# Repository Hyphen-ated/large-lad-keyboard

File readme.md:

## Large Lad Keyboard

148 key hotswap keyboard with a Standard US layout at the core. 

Two rows of function keys, 21 keys to the left, and some extras filling in the top right, along with a rotary encoder.

Nobody is selling this keyboard. KiCad project files are in this repo. If you want one you need to place an order at a PCB fabrication house for the PCB (and the plate. Or get the plate made elsewhere.) I got the plate made as a "PCB" with 1.6mm aluminum; if you want to try FR4 maybe that would work too.

I didn't design a case for this board. I simply attached two pieces of 1/2" square dowel across the top and bottom rows of holes in the plate. If you'd like to design a case I'd be happy to link it here.

* PCB: 146 x 490 mm
* Plate: 167 x 495 mm

Other materials you will need:

* 148x Through-hole diodes (1N4148)
* 147x MX switches and keycaps
* 147x Kailh hotswap sockets
* 1x set of stabilizers for a full sized keyboard
* 1x Rotary encoder, clickable. (The kind used on keyboards.)
* 1x WeAct STM32F411CEU6 V3.1 "Blackpill" (or a similar board with [the same pinout](/blackpill.png)

If I were to make a rev 2 of this, I would enlarge the stab holes in the plate. I had a rough time getting it to fit and I needed to file down a few edges in the plate. I also intended the plate to have (black) soldermask on top, but I messed that up so the top is bare aluminum right now. (The plate also has a few plated holes in it that don't do anything. This was recommended to me as a way to make PCB fab houses less likely to reject the design for not looking like a PCB. I'm not sure why a business would want to not take someone's money in this way, but whatever.)

Assembly: solder in the diodes and encoder on top, sockets and MCU on bottom. (I used peel-away strips for the MCU to help reduce the vertical size of the overall build while having the MCU socketed for easy removal.) Then attach your stabs to the PCB, put the plate on, and put the switches in. The switches are the only thing holding the PCB up. Then figure out how to mount the plate to some kind of case or just use pieces of wood like I did.

It works with QMK firmware, see my fork here: https://github.com/Hyphen-ated/qmk_firmware

The matrix is a bit of an [unholy nightmare](/keyboard-layout-colors.png) at 12x13. It needs to be much squarer than the layout actually is, because there aren't enough pins otherwise.

Loading firmware: 
* On the blackpill, hold BOOT and press NRST, then release both
* Open STM32CubeProgrammer. Make sure it's connected to the blackpill on the right under "usb configuration"
* Click "open file" and load the QMK hex file built for this board
* Click "download"

Shoutouts to [ai03](https://wiki.ai03.com/books/pcb-design/page/pcb-guide-part-1---preparations), https://github.com/piit79/Kicad-STM32, https://github.com/chgray/daprice-keyswitches, https://github.com/daprice/keyswitches.pretty, http://builder.swillkb.com/, http://www.keyboard-layout-editor.com/

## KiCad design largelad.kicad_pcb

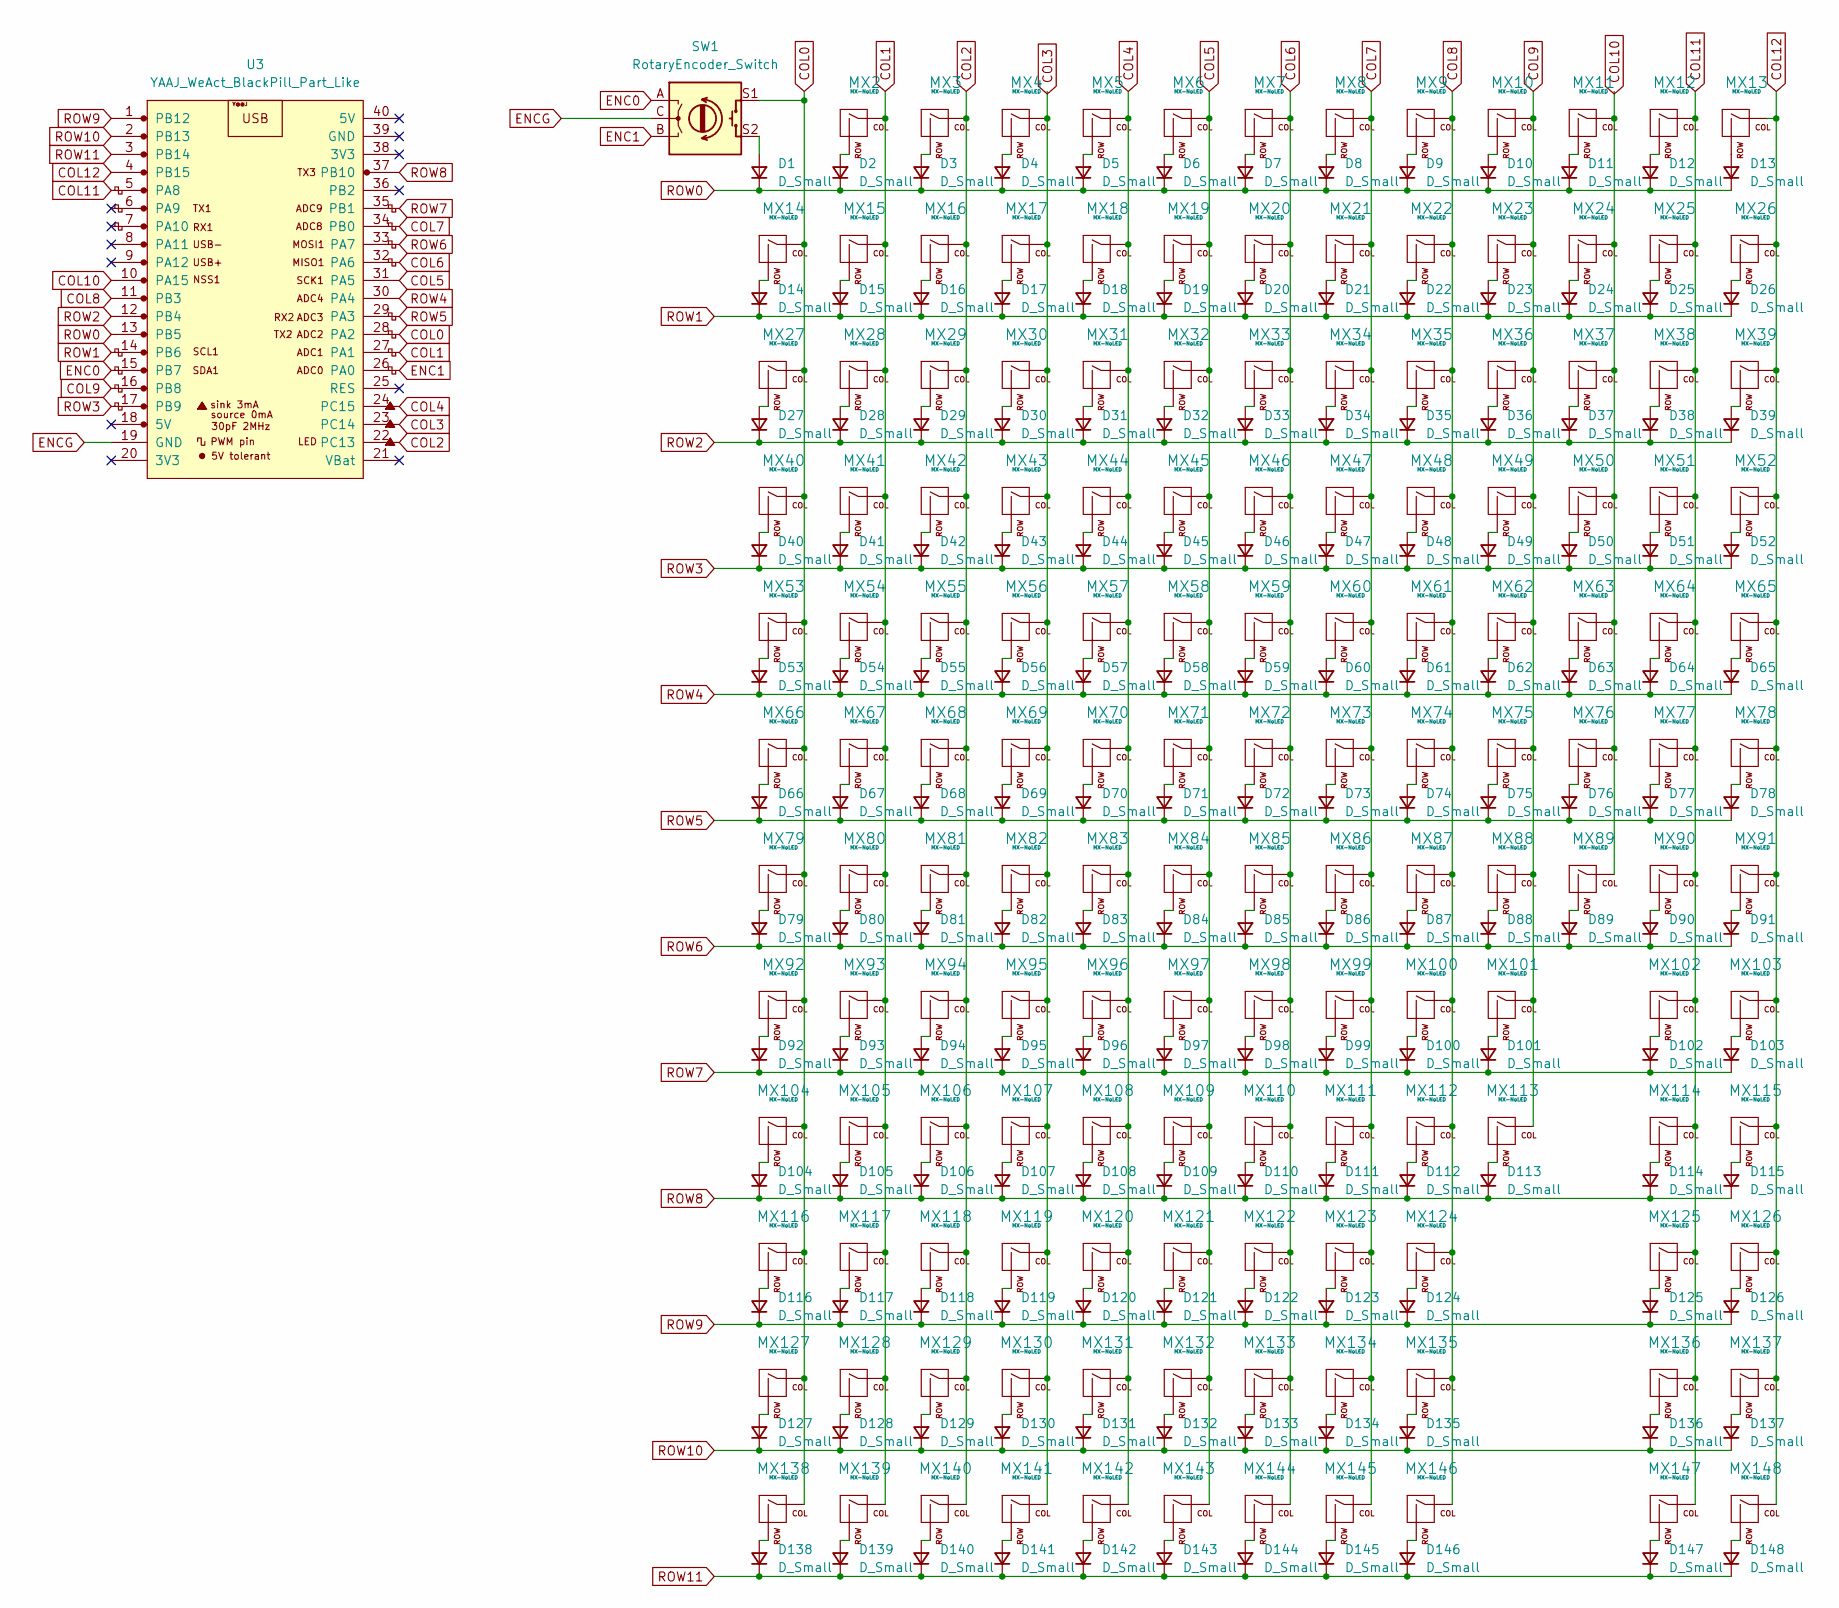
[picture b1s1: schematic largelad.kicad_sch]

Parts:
D1, D2, D3, D4, D5, D6, D7, D8, D9, D10, D11, D12, D13, D14, D15, D16, D17, D18, D19, D20, D21, D22, D23, D24, D25, D26, D27, D28, D29, D30, D31, D32, D33, D34, D35, D36, D37, D38, D39, D40, D41, D42, D43, D44, D45, D46, D47, D48, D49, D50, D51, D52, D53, D54, D55, D56, D57, D58, D59, D60, D61, D62, D63, D64, D65, D66, D67, D68, D69, D70, D71, D72, D73, D74, D75, D76, D77, D78, D79, D80, D81, D82, D83, D84, D85, D86, D87, D88, D89, D90, D91, D92, D93, D94, D95, D96, D97, D98, D99, D100, D101, D102, D103, D104, D105, D106, D107, D108, D109, D110, D111, D112, D113, D114, D115, D116, D117, D118, D119, D120, D121, D122, D123, D124, D125, D126, D127, D128, D129, D130, D131, D132, D133, D134, D135, D136, D137, D138, D139, D140, D141, D142, D143, D144, D145, D146, D147, D148: D_Small; D_DO-35_SOD27_P7.62mm_Horizontal
MX2, MX3, MX4, MX5, MX6, MX7, MX8, MX9, MX10, MX11, MX12, MX13, MX14, MX15, MX16, MX17, MX18, MX19, MX20, MX21, MX22, MX23, MX24, MX25, MX26, MX27, MX28, MX29, MX30, MX31, MX32, MX33, MX34, MX35, MX36, MX37, MX38, MX39, MX40, MX41, MX42, MX43, MX44, MX45, MX46, MX47, MX48, MX49, MX50, MX51, MX52, MX53, MX54, MX55, MX56, MX57, MX58, MX59, MX60, MX61, MX62, MX63, MX64, MX65, MX66, MX67, MX68, MX69, MX70, MX71, MX72, MX73, MX74, MX75, MX76, MX77, MX78, MX79, MX80, MX81, MX82, MX83, MX84, MX85, MX86, MX87, MX88, MX89, MX90, MX91, MX92, MX93, MX94, MX95, MX96, MX97, MX98, MX99, MX100, MX101, MX102, MX103, MX104, MX105, MX106, MX107, MX108, MX109, MX110, MX111, MX112, MX113, MX114, MX115, MX116, MX117, MX118, MX119, MX120, MX121, MX122, MX123, MX124, MX125, MX126, MX127, MX128, MX129, MX130, MX131, MX132, MX133, MX134, MX135, MX136, MX137, MX138, MX139, MX140, MX141, MX142, MX143, MX144, MX145, MX146, MX147, MX148: MX-NoLED; Kailh_socket_MX
SW1: RotaryEncoder_Switch; RotaryEncoder_Alps_EC11E-Switch_Vertical_H20mm_CircularMoun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
U3: YAAJ_WeAct_BlackPill_Part_Like; YAAJ_WeAct_BlackPill_2

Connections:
COL0: MX14.1 (COL), MX27.1 (COL), MX40.1 (COL), MX53.1 (COL), MX66.1 (COL), MX79.1 (COL), MX92.1 (COL), MX104.1 (COL), MX116.1 (COL), MX127.1 (COL), MX138.1 (COL), SW1.S1, U3.28 (PA2)
COL1: MX2.1 (COL), MX15.1 (COL), MX28.1 (COL), MX41.1 (COL), MX54.1 (COL), MX67.1 (COL), MX80.1 (COL), MX93.1 (COL), MX105.1 (COL), MX117.1 (COL), MX128.1 (COL), MX139.1 (COL), U3.27 (PA1)
COL2: MX3.1 (COL), MX16.1 (COL), MX29.1 (COL), MX42.1 (COL), MX55.1 (COL), MX68.1 (COL), MX81.1 (COL), MX94.1 (COL), MX106.1 (COL), MX118.1 (COL), MX129.1 (COL), MX140.1 (COL), U3.22 (PC13)
COL3: MX4.1 (COL), MX17.1 (COL), MX30.1 (COL), MX43.1 (COL), MX56.1 (COL), MX69.1 (COL), MX82.1 (COL), MX95.1 (COL), MX107.1 (COL), MX119.1 (COL), MX130.1 (COL), MX141.1 (COL), U3.23 (PC14)
COL4: MX5.1 (COL), MX18.1 (COL), MX31.1 (COL), MX44.1 (COL), MX57.1 (COL), MX70.1 (COL), MX83.1 (COL), MX96.1 (COL), MX108.1 (COL), MX120.1 (COL), MX131.1 (COL), MX142.1 (COL), U3.24 (PC15)
COL5: MX6.1 (COL), MX19.1 (COL), MX32.1 (COL), MX45.1 (COL), MX58.1 (COL), MX71.1 (COL), MX84.1 (COL), MX97.1 (COL), MX109.1 (COL), MX121.1 (COL), MX132.1 (COL), MX143.1 (COL), U3.31 (PA5)
COL6: MX7.1 (COL), MX20.1 (COL), MX33.1 (COL), MX46.1 (COL), MX59.1 (COL), MX72.1 (COL), MX85.1 (COL), MX98.1 (COL), MX110.1 (COL), MX122.1 (COL), MX133.1 (COL), MX144.1 (COL), U3.32 (PA6)
COL7: MX8.1 (COL), MX21.1 (COL), MX34.1 (COL), MX47.1 (COL), MX60.1 (COL), MX73.1 (COL), MX86.1 (COL), MX99.1 (COL), MX111.1 (COL), MX123.1 (COL), MX134.1 (COL), MX145.1 (COL), U3.34 (PB0)
COL8: MX9.1 (COL), MX22.1 (COL), MX35.1 (COL), MX48.1 (COL), MX61.1 (COL), MX74.1 (COL), MX87.1 (COL), MX100.1 (COL), MX112.1 (COL), MX124.1 (COL), MX135.1 (COL), MX146.1 (COL), U3.11 (PB3)
COL9: MX10.1 (COL), MX23.1 (COL), MX36.1 (COL), MX49.1 (COL), MX62.1 (COL), MX75.1 (COL), MX88.1 (COL), MX101.1 (COL), MX113.1 (COL), U3.16 (PB8)
COL10: MX11.1 (COL), MX24.1 (COL), MX37.1 (COL), MX50.1 (COL), MX63.1 (COL), MX76.1 (COL), MX89.1 (COL), U3.10 (PA15)
COL11: MX12.1 (COL), MX25.1 (COL), MX38.1 (COL), MX51.1 (COL), MX64.1 (COL), MX77.1 (COL), MX90.1 (COL), MX102.1 (COL), MX114.1 (COL), MX125.1 (COL), MX136.1 (COL), MX147.1 (COL), U3.5 (PA8)
COL12: MX13.1 (COL), MX26.1 (COL), MX39.1 (COL), MX52.1 (COL), MX65.1 (COL), MX78.1 (COL), MX91.1 (COL), MX103.1 (COL), MX115.1 (COL), MX126.1 (COL), MX137.1 (COL), MX148.1 (COL), U3.4 (PB15)
ENC0: SW1.A, U3.15 (PB7)
ENC1: SW1.B, U3.26 (PA0)
ENCG: SW1.C, U3.19 (GND)
unnamed: D1.2 (A), SW1.S2
unnamed: D2.2 (A), MX2.2 (ROW)
unnamed: D3.2 (A), MX3.2 (ROW)
unnamed: D4.2 (A), MX4.2 (ROW)
unnamed: D5.2 (A), MX5.2 (ROW)
unnamed: D6.2 (A), MX6.2 (ROW)
unnamed: D7.2 (A), MX7.2 (ROW)
unnamed: D8.2 (A), MX8.2 (ROW)
unnamed: D9.2 (A), MX9.2 (ROW)
unnamed: D10.2 (A), MX10.2 (ROW)
unnamed: D11.2 (A), MX11.2 (ROW)
unnamed: D12.2 (A), MX12.2 (ROW)
unnamed: D13.2 (A), MX13.2 (ROW)
unnamed: D14.2 (A), MX14.2 (ROW)
unnamed: D15.2 (A), MX15.2 (ROW)
unnamed: D16.2 (A), MX16.2 (ROW)
unnamed: D17.2 (A), MX17.2 (ROW)
unnamed: D18.2 (A), MX18.2 (ROW)
unnamed: D19.2 (A), MX19.2 (ROW)
unnamed: D20.2 (A), MX20.2 (ROW)
unnamed: D21.2 (A), MX21.2 (ROW)
unnamed: D22.2 (A), MX22.2 (ROW)
unnamed: D23.2 (A), MX23.2 (ROW)
unnamed: D24.2 (A), MX24.2 (ROW)
unnamed: D25.2 (A), MX25.2 (ROW)
unnamed: D26.2 (A), MX26.2 (ROW)
unnamed: D27.2 (A), MX27.2 (ROW)
unnamed: D28.2 (A), MX28.2 (ROW)
unnamed: D29.2 (A), MX29.2 (ROW)
unnamed: D30.2 (A), MX30.2 (ROW)
unnamed: D31.2 (A), MX31.2 (ROW)
unnamed: D32.2 (A), MX32.2 (ROW)
unnamed: D33.2 (A), MX33.2 (ROW)
unnamed: D34.2 (A), MX34.2 (ROW)
unnamed: D35.2 (A), MX35.2 (ROW)
unnamed: D36.2 (A), MX36.2 (ROW)
unnamed: D37.2 (A), MX37.2 (ROW)
unnamed: D38.2 (A), MX38.2 (ROW)
unnamed: D39.2 (A), MX39.2 (ROW)
unnamed: D40.2 (A), MX40.2 (ROW)
unnamed: D41.2 (A), MX41.2 (ROW)
unnamed: D42.2 (A), MX42.2 (ROW)
unnamed: D43.2 (A), MX43.2 (ROW)
unnamed: D44.2 (A), MX44.2 (ROW)
unnamed: D45.2 (A), MX45.2 (ROW)
unnamed: D46.2 (A), MX46.2 (ROW)
unnamed: D47.2 (A), MX47.2 (ROW)
unnamed: D48.2 (A), MX48.2 (ROW)
unnamed: D49.2 (A), MX49.2 (ROW)
unnamed: D50.2 (A), MX50.2 (ROW)
unnamed: D51.2 (A), MX51.2 (ROW)
unnamed: D52.2 (A), MX52.2 (ROW)
unnamed: D53.2 (A), MX53.2 (ROW)
unnamed: D54.2 (A), MX54.2 (ROW)
unnamed: D55.2 (A), MX55.2 (ROW)
unnamed: D56.2 (A), MX56.2 (ROW)
unnamed: D57.2 (A), MX57.2 (ROW)
unnamed: D58.2 (A), MX58.2 (ROW)
unnamed: D59.2 (A), MX59.2 (ROW)
unnamed: D60.2 (A), MX60.2 (ROW)
unnamed: D61.2 (A), MX61.2 (ROW)
unnamed: D62.2 (A), MX62.2 (ROW)
unnamed: D63.2 (A), MX63.2 (ROW)
unnamed: D64.2 (A), MX64.2 (ROW)
unnamed: D65.2 (A), MX65.2 (ROW)
unnamed: D66.2 (A), MX66.2 (ROW)
unnamed: D67.2 (A), MX67.2 (ROW)
unnamed: D68.2 (A), MX68.2 (ROW)
unnamed: D69.2 (A), MX69.2 (ROW)
unnamed: D70.2 (A), MX70.2 (ROW)
unnamed: D71.2 (A), MX71.2 (ROW)
unnamed: D72.2 (A), MX72.2 (ROW)
unnamed: D73.2 (A), MX73.2 (ROW)
unnamed: D74.2 (A), MX74.2 (ROW)
unnamed: D75.2 (A), MX75.2 (ROW)
unnamed: D76.2 (A), MX76.2 (ROW)
unnamed: D77.2 (A), MX77.2 (ROW)
unnamed: D78.2 (A), MX78.2 (ROW)
unnamed: D79.2 (A), MX79.2 (ROW)
unnamed: D80.2 (A), MX80.2 (ROW)
unnamed: D81.2 (A), MX81.2 (ROW)
unnamed: D82.2 (A), MX82.2 (ROW)
unnamed: D83.2 (A), MX83.2 (ROW)
unnamed: D84.2 (A), MX84.2 (ROW)
unnamed: D85.2 (A), MX85.2 (ROW)
unnamed: D86.2 (A), MX86.2 (ROW)
unnamed: D87.2 (A), MX87.2 (ROW)
unnamed: D88.2 (A), MX88.2 (ROW)
unnamed: D89.2 (A), MX89.2 (ROW)
unnamed: D90.2 (A), MX90.2 (ROW)
unnamed: D91.2 (A), MX91.2 (ROW)
unnamed: D92.2 (A), MX92.2 (ROW)
unnamed: D93.2 (A), MX93.2 (ROW)
unnamed: D94.2 (A), MX94.2 (ROW)
unnamed: D95.2 (A), MX95.2 (ROW)
unnamed: D96.2 (A), MX96.2 (ROW)
unnamed: D97.2 (A), MX97.2 (ROW)
unnamed: D98.2 (A), MX98.2 (ROW)
unnamed: D99.2 (A), MX99.2 (ROW)
unnamed: D100.2 (A), MX100.2 (ROW)
unnamed: D101.2 (A), MX101.2 (ROW)
unnamed: D102.2 (A), MX102.2 (ROW)
unnamed: D103.2 (A), MX103.2 (ROW)
unnamed: D104.2 (A), MX104.2 (ROW)
unnamed: D105.2 (A), MX105.2 (ROW)
unnamed: D106.2 (A), MX106.2 (ROW)
unnamed: D107.2 (A), MX107.2 (ROW)
unnamed: D108.2 (A), MX108.2 (ROW)
unnamed: D109.2 (A), MX109.2 (ROW)
unnamed: D110.2 (A), MX110.2 (ROW)
unnamed: D111.2 (A), MX111.2 (ROW)
unnamed: D112.2 (A), MX112.2 (ROW)
unnamed: D113.2 (A), MX113.2 (ROW)
unnamed: D114.2 (A), MX114.2 (ROW)
unnamed: D115.2 (A), MX115.2 (ROW)
unnamed: D116.2 (A), MX116.2 (ROW)
unnamed: D117.2 (A), MX117.2 (ROW)
unnamed: D118.2 (A), MX118.2 (ROW)
unnamed: D119.2 (A), MX119.2 (ROW)
unnamed: D120.2 (A), MX120.2 (ROW)
unnamed: D121.2 (A), MX121.2 (ROW)
unnamed: D122.2 (A), MX122.2 (ROW)
unnamed: D123.2 (A), MX123.2 (ROW)
unnamed: D124.2 (A), MX124.2 (ROW)
unnamed: D125.2 (A), MX125.2 (ROW)
unnamed: D126.2 (A), MX126.2 (ROW)
unnamed: D127.2 (A), MX127.2 (ROW)
unnamed: D128.2 (A), MX128.2 (ROW)
unnamed: D129.2 (A), MX129.2 (ROW)
unnamed: D130.2 (A), MX130.2 (ROW)
unnamed: D131.2 (A), MX131.2 (ROW)
unnamed: D132.2 (A), MX132.2 (ROW)
unnamed: D133.2 (A), MX133.2 (ROW)
unnamed: D134.2 (A), MX134.2 (ROW)
unnamed: D135.2 (A), MX135.2 (ROW)
unnamed: D136.2 (A), MX136.2 (ROW)
unnamed: D137.2 (A), MX137.2 (ROW)
unnamed: D138.2 (A), MX138.2 (ROW)
unnamed: D139.2 (A), MX139.2 (ROW)
unnamed: D140.2 (A), MX140.2 (ROW)
unnamed: D141.2 (A), MX141.2 (ROW)
unnamed: D142.2 (A), MX142.2 (ROW)
unnamed: D143.2 (A), MX143.2 (ROW)
unnamed: D144.2 (A), MX144.2 (ROW)
unnamed: D145.2 (A), MX145.2 (ROW)
unnamed: D146.2 (A), MX146.2 (ROW)
unnamed: D147.2 (A), MX147.2 (ROW)
unnamed: D148.2 (A), MX148.2 (ROW)
ROW0: D1.1 (K), D2.1 (K), D3.1 (K), D4.1 (K), D5.1 (K), D6.1 (K), D7.1 (K), D8.1 (K), D9.1 (K), D10.1 (K), D11.1 (K), D12.1 (K), D13.1 (K), U3.13 (PB5)
ROW1: D14.1 (K), D15.1 (K), D16.1 (K), D17.1 (K), D18.1 (K), D19.1 (K), D20.1 (K), D21.1 (K), D22.1 (K), D23.1 (K), D24.1 (K), D25.1 (K), D26.1 (K), U3.14 (PB6)
ROW2: D27.1 (K), D28.1 (K), D29.1 (K), D30.1 (K), D31.1 (K), D32.1 (K), D33.1 (K), D34.1 (K), D35.1 (K), D36.1 (K), D37.1 (K), D38.1 (K), D39.1 (K), U3.12 (PB4)
ROW3: D40.1 (K), D41.1 (K), D42.1 (K), D43.1 (K), D44.1 (K), D45.1 (K), D46.1 (K), D47.1 (K), D48.1 (K), D49.1 (K), D50.1 (K), D51.1 (K), D52.1 (K), U3.17 (PB9)
ROW4: D53.1 (K), D54.1 (K), D55.1 (K), D56.1 (K), D57.1 (K), D58.1 (K), D59.1 (K), D60.1 (K), D61.1 (K), D62.1 (K), D63.1 (K), D64.1 (K), D65.1 (K), U3.30 (PA4)
ROW5: D66.1 (K), D67.1 (K), D68.1 (K), D69.1 (K), D70.1 (K), D71.1 (K), D72.1 (K), D73.1 (K), D74.1 (K), D75.1 (K), D76.1 (K), D77.1 (K), D78.1 (K), U3.29 (PA3)
ROW6: D79.1 (K), D80.1 (K), D81.1 (K), D82.1 (K), D83.1 (K), D84.1 (K), D85.1 (K), D86.1 (K), D87.1 (K), D88.1 (K), D89.1 (K), D90.1 (K), D91.1 (K), U3.33 (PA7)
ROW7: D92.1 (K), D93.1 (K), D94.1 (K), D95.1 (K), D96.1 (K), D97.1 (K), D98.1 (K), D99.1 (K), D100.1 (K), D101.1 (K), D102.1 (K), D103.1 (K), U3.35 (PB1)
ROW8: D104.1 (K), D105.1 (K), D106.1 (K), D107.1 (K), D108.1 (K), D109.1 (K), D110.1 (K), D111.1 (K), D112.1 (K), D113.1 (K), D114.1 (K), D115.1 (K), U3.37 (PB10)
ROW9: D116.1 (K), D117.1 (K), D118.1 (K), D119.1 (K), D120.1 (K), D121.1 (K), D122.1 (K), D123.1 (K), D124.1 (K), D125.1 (K), D126.1 (K), U3.1 (PB12)
ROW10: D127.1 (K), D128.1 (K), D129.1 (K), D130.1 (K), D131.1 (K), D132.1 (K), D133.1 (K), D134.1 (K), D135.1 (K), D136.1 (K), D137.1 (K), U3.2 (PB13)
ROW11: D138.1 (K), D139.1 (K), D140.1 (K), D141.1 (K), D142.1 (K), D143.1 (K), D144.1 (K), D145.1 (K), D146.1 (K), D147.1 (K), D148.1 (K), U3.3 (PB14)

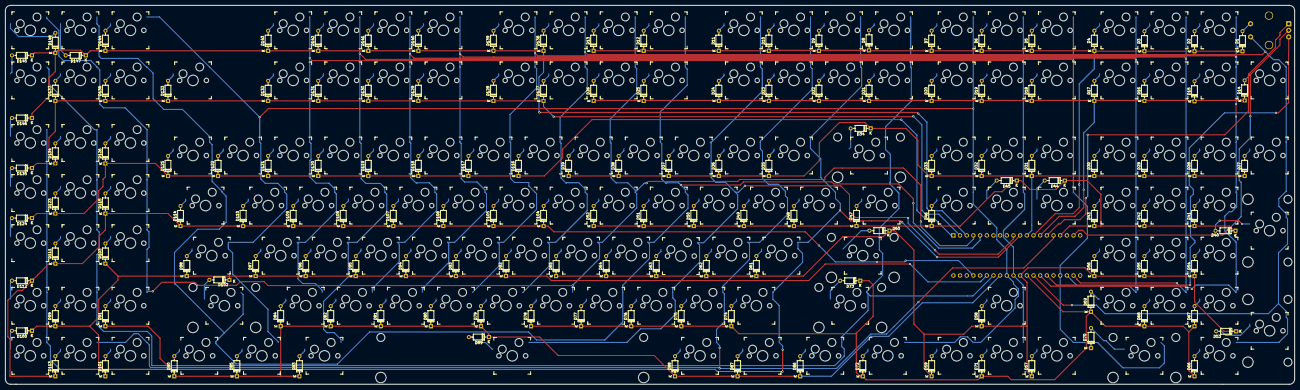
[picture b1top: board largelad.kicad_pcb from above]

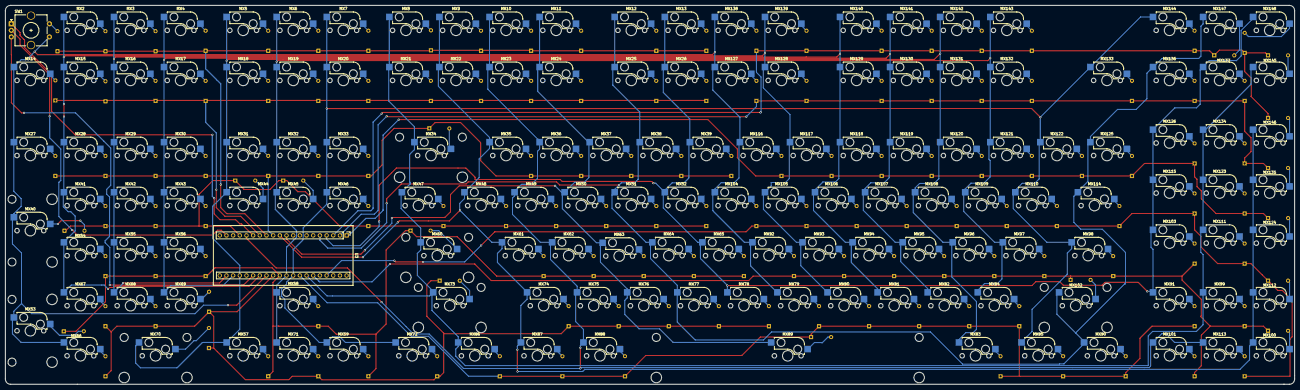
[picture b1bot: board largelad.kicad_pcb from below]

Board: 2 copper layers, 490.5 x 144.1 mm, 297 parts (2 on the bottom side), 176 nets.

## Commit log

2022-05-28 initial commit, schematic and parts but no traces
2022-05-28 flip diodes and blackpill to the top
2022-05-28 connect up the columns
2022-05-29 route the whole matrix
2022-05-30 add edge cuts, move some diodes away from stab holes
2022-06-09 shrink pcb bottom a little
2022-06-27 update plate and readme
2022-06-27 rename plate dirs to be clearer
2022-06-27 remove unused library
